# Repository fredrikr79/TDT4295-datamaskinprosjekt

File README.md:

## Structure

### MCU

The source code for the microcontroller

### FPGA

The source code for the FPGA

### PCB

The schematics for the PCB

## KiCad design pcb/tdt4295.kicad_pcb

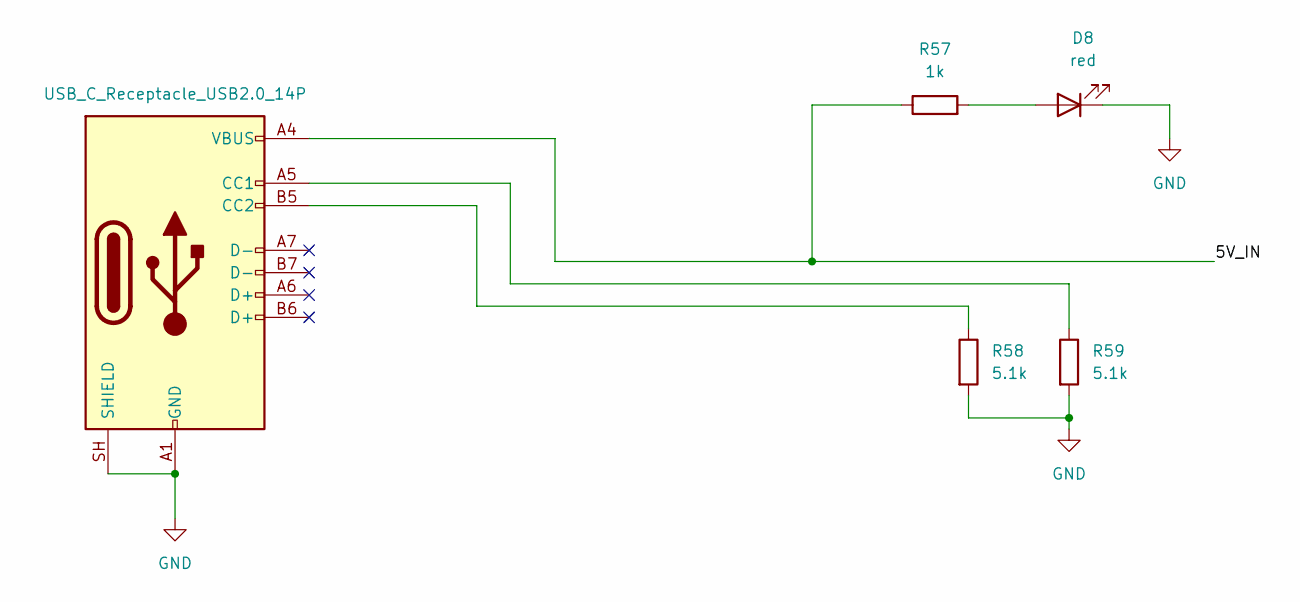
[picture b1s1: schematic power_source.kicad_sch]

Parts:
D8: red; LED_0805_2012Metric_Pad1.15x1.40mm_HandSolder
J7: USB_C_Receptacle_USB2.0_14P; USB_C_Receptacle_GCT_USB4105-xx-A_16P_TopMnt_Horizontal
R57: 1k; R_0805_2012Metric_Pad1.20x1.40mm_HandSolder
R58, R59: 5.1k; R_0805_2012Metric_Pad1.20x1.40mm_HandSolder

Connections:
5V_IN: J7.A4 (VBUS), J7.A9 (VBUS), J7.B4 (VBUS), J7.B9 (VBUS), R57.1; also elsewhere on the board
GND: D8.1 (K), J7.A1 (GND), J7.A12 (GND), J7.B1 (GND), J7.B12 (GND), J7.SH (SHIELD), R58.2, R59.2; also elsewhere on the board
unnamed: D8.2 (A), R57.2
unnamed: J7.A5 (CC1), R59.1
unnamed: J7.B5 (CC2), R58.1

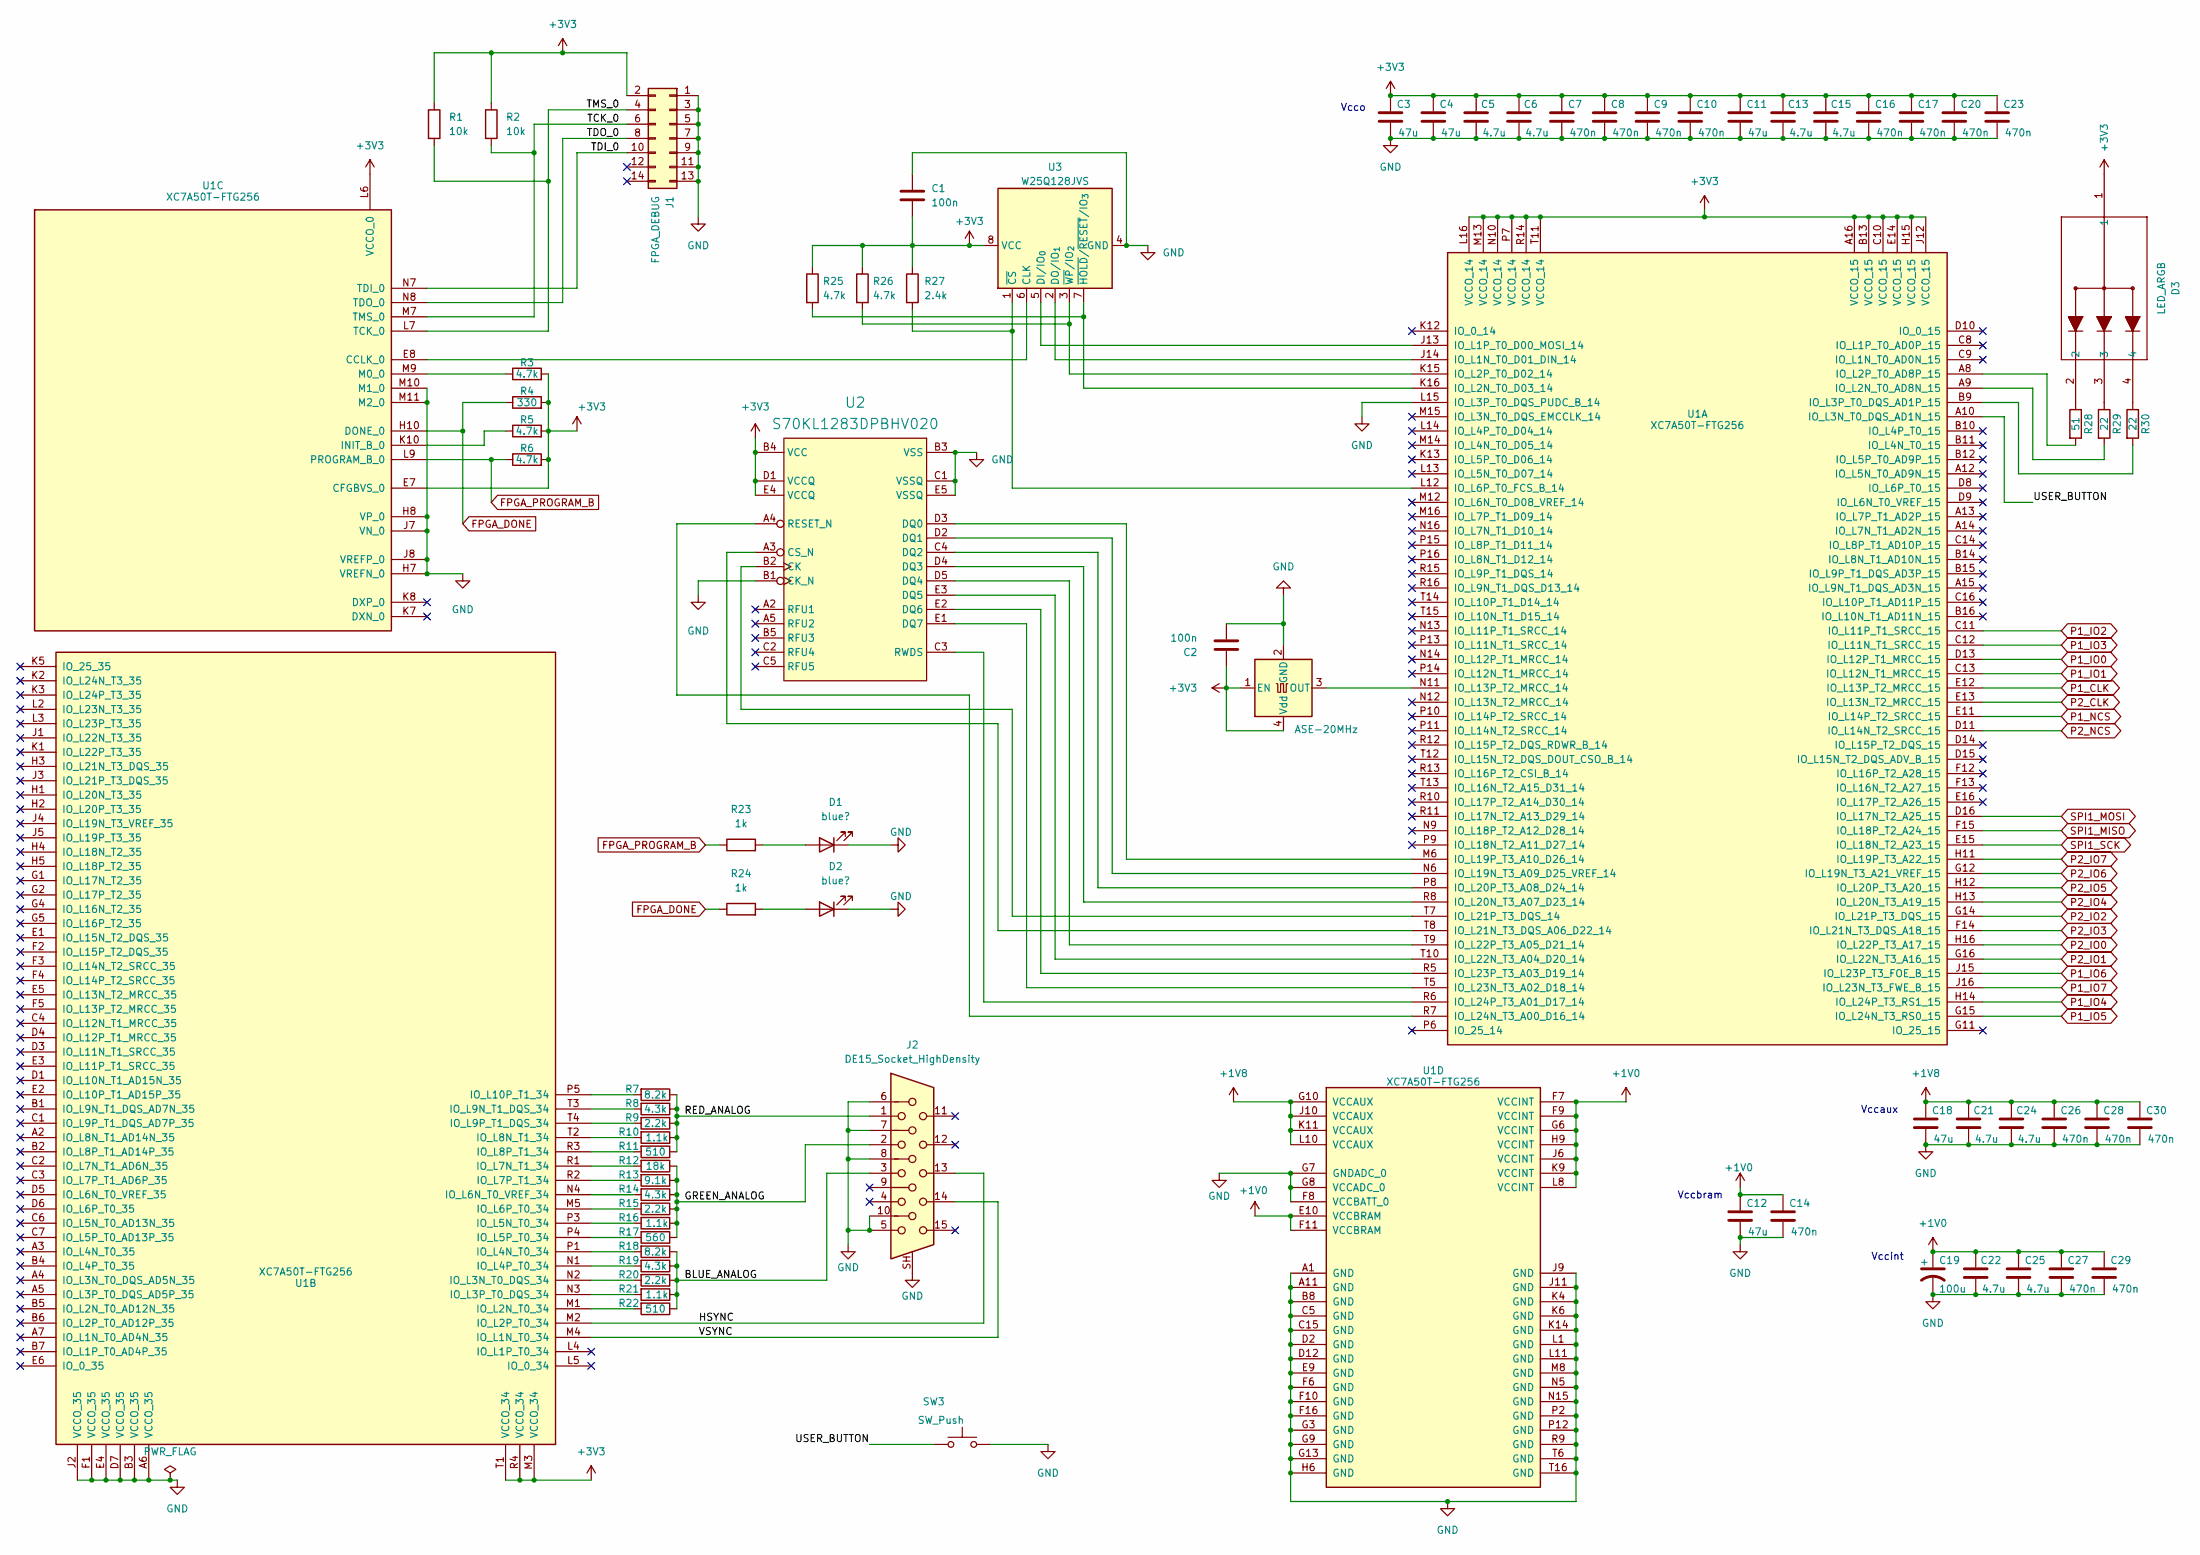
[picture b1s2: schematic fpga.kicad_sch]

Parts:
C1, C2: 100n; C_0805_2012Metric_Pad1.18x1.45mm_HandSolder
C3, C4, C11, C12, C18: 47u; C_0805_2012Metric_Pad1.18x1.45mm_HandSolder
C5, C6, C13, C15, C21, C22, C24, C25: 4.7u; C_0805_2012Metric_Pad1.18x1.45mm_HandSolder
C7, C8, C9, C10, C14, C16, C17, C20, C23, C26, C27, C28, C29, C30: 470n; C_0805_2012Metric_Pad1.18x1.45mm_HandSolder
C19: 100u; C_0805_2012Metric_Pad1.18x1.45mm_HandSolder
D1, D2: blue?; LED_0805_2012Metric_Pad1.15x1.40mm_HandSolder
D3: LED_ARGB; SON4_APTF1616LSEEZGKQBKC_KNB
J1: FPGA_DEBUG; PinHeader_2x07_P2.54mm_Vertical
J2: DE15_Socket_HighDensity; AMPHENOL_L77HDE15SD1CH4FVGA
R1, R2: 10k; R_0805_2012Metric_Pad1.20x1.40mm_HandSolder
R3, R5, R6, R25, R26: 4.7k; R_0805_2012Metric_Pad1.20x1.40mm_HandSolder
R4: 330; R_0805_2012Metric_Pad1.20x1.40mm_HandSolder
R7, R18: 8.2k; R_0805_2012Metric_Pad1.20x1.40mm_HandSolder
R8, R14, R19: 4.3k; R_0805_2012Metric_Pad1.20x1.40mm_HandSolder
R9, R15, R20: 2.2k; R_0805_2012Metric_Pad1.20x1.40mm_HandSolder
R10, R16, R21: 1.1k; R_0805_2012Metric_Pad1.20x1.40mm_HandSolder
R11, R22: 510; R_0805_2012Metric_Pad1.20x1.40mm_HandSolder
R12: 18k; R_0805_2012Metric_Pad1.20x1.40mm_HandSolder
R13: 9.1k; R_0805_2012Metric_Pad1.20x1.40mm_HandSolder
R17: 560; R_0805_2012Metric_Pad1.20x1.40mm_HandSolder
R23, R24: 1k; R_0805_2012Metric_Pad1.20x1.40mm_HandSolder
R27: 2.4k; R_0805_2012Metric_Pad1.20x1.40mm_HandSolder
R28: 51; R_0805_2012Metric_Pad1.20x1.40mm_HandSolder
R29, R30: 22; R_0805_2012Metric_Pad1.20x1.40mm_HandSolder
SW3: SW_Push; SW_Push_1P1T_NO_CK_KSC6xxG
U1: XC7A50T-FTG256; Xilinx_FTG256
U2: S70KL1283DPBHV020; BGA24C100P5X5_600X800X100
U3: W25Q128JVS; SOIC-8_5.3x5.3mm_P1.27mm
Y1: ASE-20MHz; Oscillator_SMD_Abracon_ASV-4Pin_7.0x5.1mm_HandSoldering

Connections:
+1V0: C12.1, C14.1, C19.1, C22.1, C25.1, C27.1, C29.1, U1.E10 (VCCBRAM), U1.F7 (VCCINT), U1.F9 (VCCINT), U1.F11 (VCCBRAM), U1.G6 (VCCINT), U1.H9 (VCCINT), U1.J6 (VCCINT), U1.K9 (VCCINT), U1.L8 (VCCINT); also elsewhere on the board
+1V8: C18.1, C21.1, C24.1, C26.1, C28.1, C30.1, U1.G10 (VCCAUX), U1.J10 (VCCAUX), U1.K11 (VCCAUX), U1.L10 (VCCAUX); also elsewhere on the board
+3V3: C1.2, C2.1, C3.1, C4.1, C5.1, C6.1, C7.1, C8.1, C9.1, C10.1, C11.1, C13.1, C15.1, C16.1, C17.1, C20.1, C23.1, D3.1, J1.2, R1.1, R2.1, R3.2, R4.2, R5.2, R6.2, R25.1, R26.1, R27.1, U1.A16 (VCCO_15), U1.B13 (VCCO_15), U1.C10 (VCCO_15), U1.E7 (CFGBVS_0), U1.E14 (VCCO_15), U1.H15 (VCCO_15), U1.J12 (VCCO_15), U1.L6 (VCCO_0), U1.L16 (VCCO_14), U1.M3 (VCCO_34), U1.M13 (VCCO_14), U1.N10 (VCCO_14), U1.P7 (VCCO_14), U1.R4 (VCCO_34), U1.R14 (VCCO_14), U1.T1 (VCCO_34), U1.T11 (VCCO_14), U2.B4 (VCC), U2.D1 (VCCQ), U2.E4 (VCCQ), U3.8 (VCC), Y1.1 (EN), Y1.4 (Vdd); also elsewhere on the board
/fpga/BLUE_ANALOG: J2.3, R18.1, R19.1, R20.1, R21.1, R22.1
/fpga/GREEN_ANALOG: J2.2, R12.1, R13.1, R14.1, R15.1, R16.1, R17.1
/fpga/HSYNC: J2.13, U1.M2 (IO_L2P_T0_34)
/fpga/RED_ANALOG: J2.1, R7.1, R8.1, R9.1, R10.1, R11.1
/fpga/TCK_0: J1.6, R2.2, U1.M7 (TMS_0)
/fpga/TDI_0: J1.10, U1.N7 (TDI_0)
/fpga/TDO_0: J1.8, U1.N8 (TDO_0)
/fpga/TMS_0: J1.4, R1.2, U1.L7 (TCK_0)
/fpga/USER_BUTTON: SW3.1, U1.A10 (IO_L3N_T0_DQS_AD1N_15)
/fpga/VSYNC: J2.14, U1.M4 (IO_L1N_T0_34)
FPGA_DONE: R4.1, R24.1, U1.H10 (DONE_0); also elsewhere on the board
FPGA_PROGRAM_B: R6.1, R23.1, U1.L9 (PROGRAM_B_0); also elsewhere on the board
GND: C1.1, C2.2, C3.2, C4.2, C5.2, C6.2, C7.2, C8.2, C9.2, C10.2, C11.2, C12.2, C13.2, C14.2, C15.2, C16.2, C17.2, C18.2, C19.2, C20.2, C21.2, C22.2, C23.2, C24.2, C25.2, C26.2, C27.2, C28.2, C29.2, C30.2, D1.1 (K), D2.1 (K), J1.1, J1.3, J1.5, J1.7, J1.9, J1.11, J1.13, J2.5, J2.6, J2.7, J2.8, J2.10, J2.SH, SW3.2, U1.A1 (GND), U1.A6 (VCCO_35), U1.A11 (GND), U1.B3 (VCCO_35), U1.B8 (GND), U1.C5 (GND), U1.C15 (GND), U1.D2 (GND), U1.D7 (VCCO_35), U1.D12 (GND), U1.E4 (VCCO_35), U1.E9 (GND), U1.F1 (VCCO_35), U1.F6 (GND), U1.F8 (VCCBATT_0), U1.F10 (GND), U1.F16 (GND), U1.G3 (GND), U1.G7 (GNDADC_0), U1.G8 (VCCADC_0), U1.G9 (GND), U1.G13 (GND), U1.H6 (GND), U1.H7 (VREFN_0), U1.H8 (VP_0), U1.J2 (VCCO_35), U1.J7 (VN_0), U1.J8 (VREFP_0), U1.J9 (GND), U1.J11 (GND), U1.K4 (GND), U1.K6 (GND), U1.K14 (GND), U1.L1 (GND), U1.L11 (GND), U1.L15 (IO_L3P_T0_DQS_PUDC_B_14), U1.M8 (GND), U1.M10 (M1_0), U1.M11 (M2_0), U1.N5 (GND), U1.N15 (GND), U1.P2 (GND), U1.P12 (GND), U1.R9 (GND), U1.T6 (GND), U1.T16 (GND), U2.B1 (CK_N), U2.B3 (VSS), U2.C1 (VSSQ), U2.E5 (VSSQ), U3.4 (GND), Y1.2 (GND); also elsewhere on the board
unnamed: D1.2 (A), R23.2
unnamed: D2.2 (A), R24.2
unnamed: D3.2, R28.1
unnamed: D3.3, R29.1
unnamed: D3.4, R30.1
unnamed: U1.J14 (IO_L1N_T0_D01_DIN_14), U3.2 (DO/IO_{1})
unnamed: U1.J13 (IO_L1P_T0_D00_MOSI_14), U3.5 (DI/IO_{0})
unnamed: R29.2, U1.A9 (IO_L2N_T0_AD8N_15)
unnamed: R25.2, U1.K16 (IO_L2N_T0_D03_14), U3.7 (~HOLD/~RESET/IO_{3})
unnamed: R28.2, U1.A8 (IO_L2P_T0_AD8P_15)
unnamed: R26.2, U1.K15 (IO_L2P_T0_D02_14), U3.3 (~WP/IO_{2})
unnamed: R30.2, U1.B9 (IO_L3P_T0_DQS_AD1P_15)
unnamed: R27.2, U1.L12 (IO_L6P_T0_FCS_B_14), U3.1 (~CS)
unnamed: U1.N11 (IO_L13P_T2_MRCC_14), Y1.3 (OUT)
unnamed: U1.N6 (IO_L19N_T3_A09_D25_VREF_14), U2.D2 (DQ1)
unnamed: U1.M6 (IO_L19P_T3_A10_D26_14), U2.D3 (DQ0)
unnamed: U1.R8 (IO_L20N_T3_A07_D23_14), U2.D4 (DQ3)
unnamed: U1.P8 (IO_L20P_T3_A08_D24_14), U2.C4 (DQ2)
unnamed: U1.T8 (IO_L21N_T3_DQS_A06_D22_14), U2.A3 (CS_N)
unnamed: U1.T7 (IO_L21P_T3_DQS_14), U2.B2 (CK)
unnamed: U1.T10 (IO_L22N_T3_A04_D20_14), U2.E3 (DQ5)
unnamed: U1.T9 (IO_L22P_T3_A05_D21_14), U2.D5 (DQ4)
unnamed: U1.T5 (IO_L23N_T3_A02_D18_14), U2.E1 (DQ7)
unnamed: U1.R5 (IO_L23P_T3_A03_D19_14), U2.E2 (DQ6)
unnamed: U1.R7 (IO_L24N_T3_A00_D16_14), U2.A4 (RESET_N)
unnamed: U1.R6 (IO_L24P_T3_A01_D17_14), U2.C3 (RWDS)
unnamed: R22.2, U1.M1 (IO_L2N_T0_34)
unnamed: R20.2, U1.N2 (IO_L3N_T0_DQS_34)
unnamed: R21.2, U1.N3 (IO_L3P_T0_DQS_34)
unnamed: R18.2, U1.P1 (IO_L4N_T0_34)
unnamed: R19.2, U1.N1 (IO_L4P_T0_34)
unnamed: R16.2, U1.P3 (IO_L5N_T0_34)
unnamed: R17.2, U1.P4 (IO_L5P_T0_34)
unnamed: R14.2, U1.N4 (IO_L6N_T0_VREF_34)
unnamed: R15.2, U1.M5 (IO_L6P_T0_34)
unnamed: R12.2, U1.R1 (IO_L7N_T1_34)
unnamed: R13.2, U1.R2 (IO_L7P_T1_34)
unnamed: R10.2, U1.T2 (IO_L8N_T1_34)
unnamed: R11.2, U1.R3 (IO_L8P_T1_34)
unnamed: R8.2, U1.T3 (IO_L9N_T1_DQS_34)
unnamed: R9.2, U1.T4 (IO_L9P_T1_DQS_34)
unnamed: R7.2, U1.P5 (IO_L10P_T1_34)
unnamed: U1.E8 (CCLK_0), U3.6 (CLK)
unnamed: R5.1, U1.K10 (INIT_B_0)
unnamed: R3.1, U1.M9 (M0_0)
P1_CLK: U1.E12 (IO_L13P_T2_MRCC_15); also elsewhere on the board
P1_IO0: U1.D13 (IO_L12P_T1_MRCC_15); also elsewhere on the board
P1_IO1: U1.C13 (IO_L12N_T1_MRCC_15); also elsewhere on the board
P1_IO2: U1.C11 (IO_L11P_T1_SRCC_15); also elsewhere on the board
P1_IO3: U1.C12 (IO_L11N_T1_SRCC_15); also elsewhere on the board
P1_IO4: U1.H14 (IO_L24P_T3_RS1_15); also elsewhere on the board
P1_IO5: U1.G15 (IO_L24N_T3_RS0_15); also elsewhere on the board
P1_IO6: U1.J15 (IO_L23P_T3_FOE_B_15); also elsewhere on the board
P1_IO7: U1.J16 (IO_L23N_T3_FWE_B_15); also elsewhere on the board
P1_NCS: U1.E11 (IO_L14P_T2_SRCC_15); also elsewhere on the board
P2_CLK: U1.E13 (IO_L13N_T2_MRCC_15); also elsewhere on the board
P2_IO0: U1.H16 (IO_L22P_T3_A17_15); also elsewhere on the board
P2_IO1: U1.G16 (IO_L22N_T3_A16_15); also elsewhere on the board
P2_IO2: U1.G14 (IO_L21P_T3_DQS_15); also elsewhere on the board
P2_IO3: U1.F14 (IO_L21N_T3_DQS_A18_15); also elsewhere on the board
P2_IO4: U1.H13 (IO_L20N_T3_A19_15); also elsewhere on the board
P2_IO5: U1.H12 (IO_L20P_T3_A20_15); also elsewhere on the board
P2_IO6: U1.G12 (IO_L19N_T3_A21_VREF_15); also elsewhere on the board
P2_IO7: U1.H11 (IO_L19P_T3_A22_15); also elsewhere on the board
P2_NCS: U1.D11 (IO_L14N_T2_SRCC_15); also elsewhere on the board
SPI1_MISO: U1.F15 (IO_L18P_T2_A24_15); also elsewhere on the board
SPI1_MOSI: U1.D16 (IO_L17N_T2_A25_15); also elsewhere on the board
SPI1_SCK: U1.E15 (IO_L18N_T2_A23_15); also elsewhere on the board

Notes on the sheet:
Vccbram
Vccaux
Vccint
Vcco

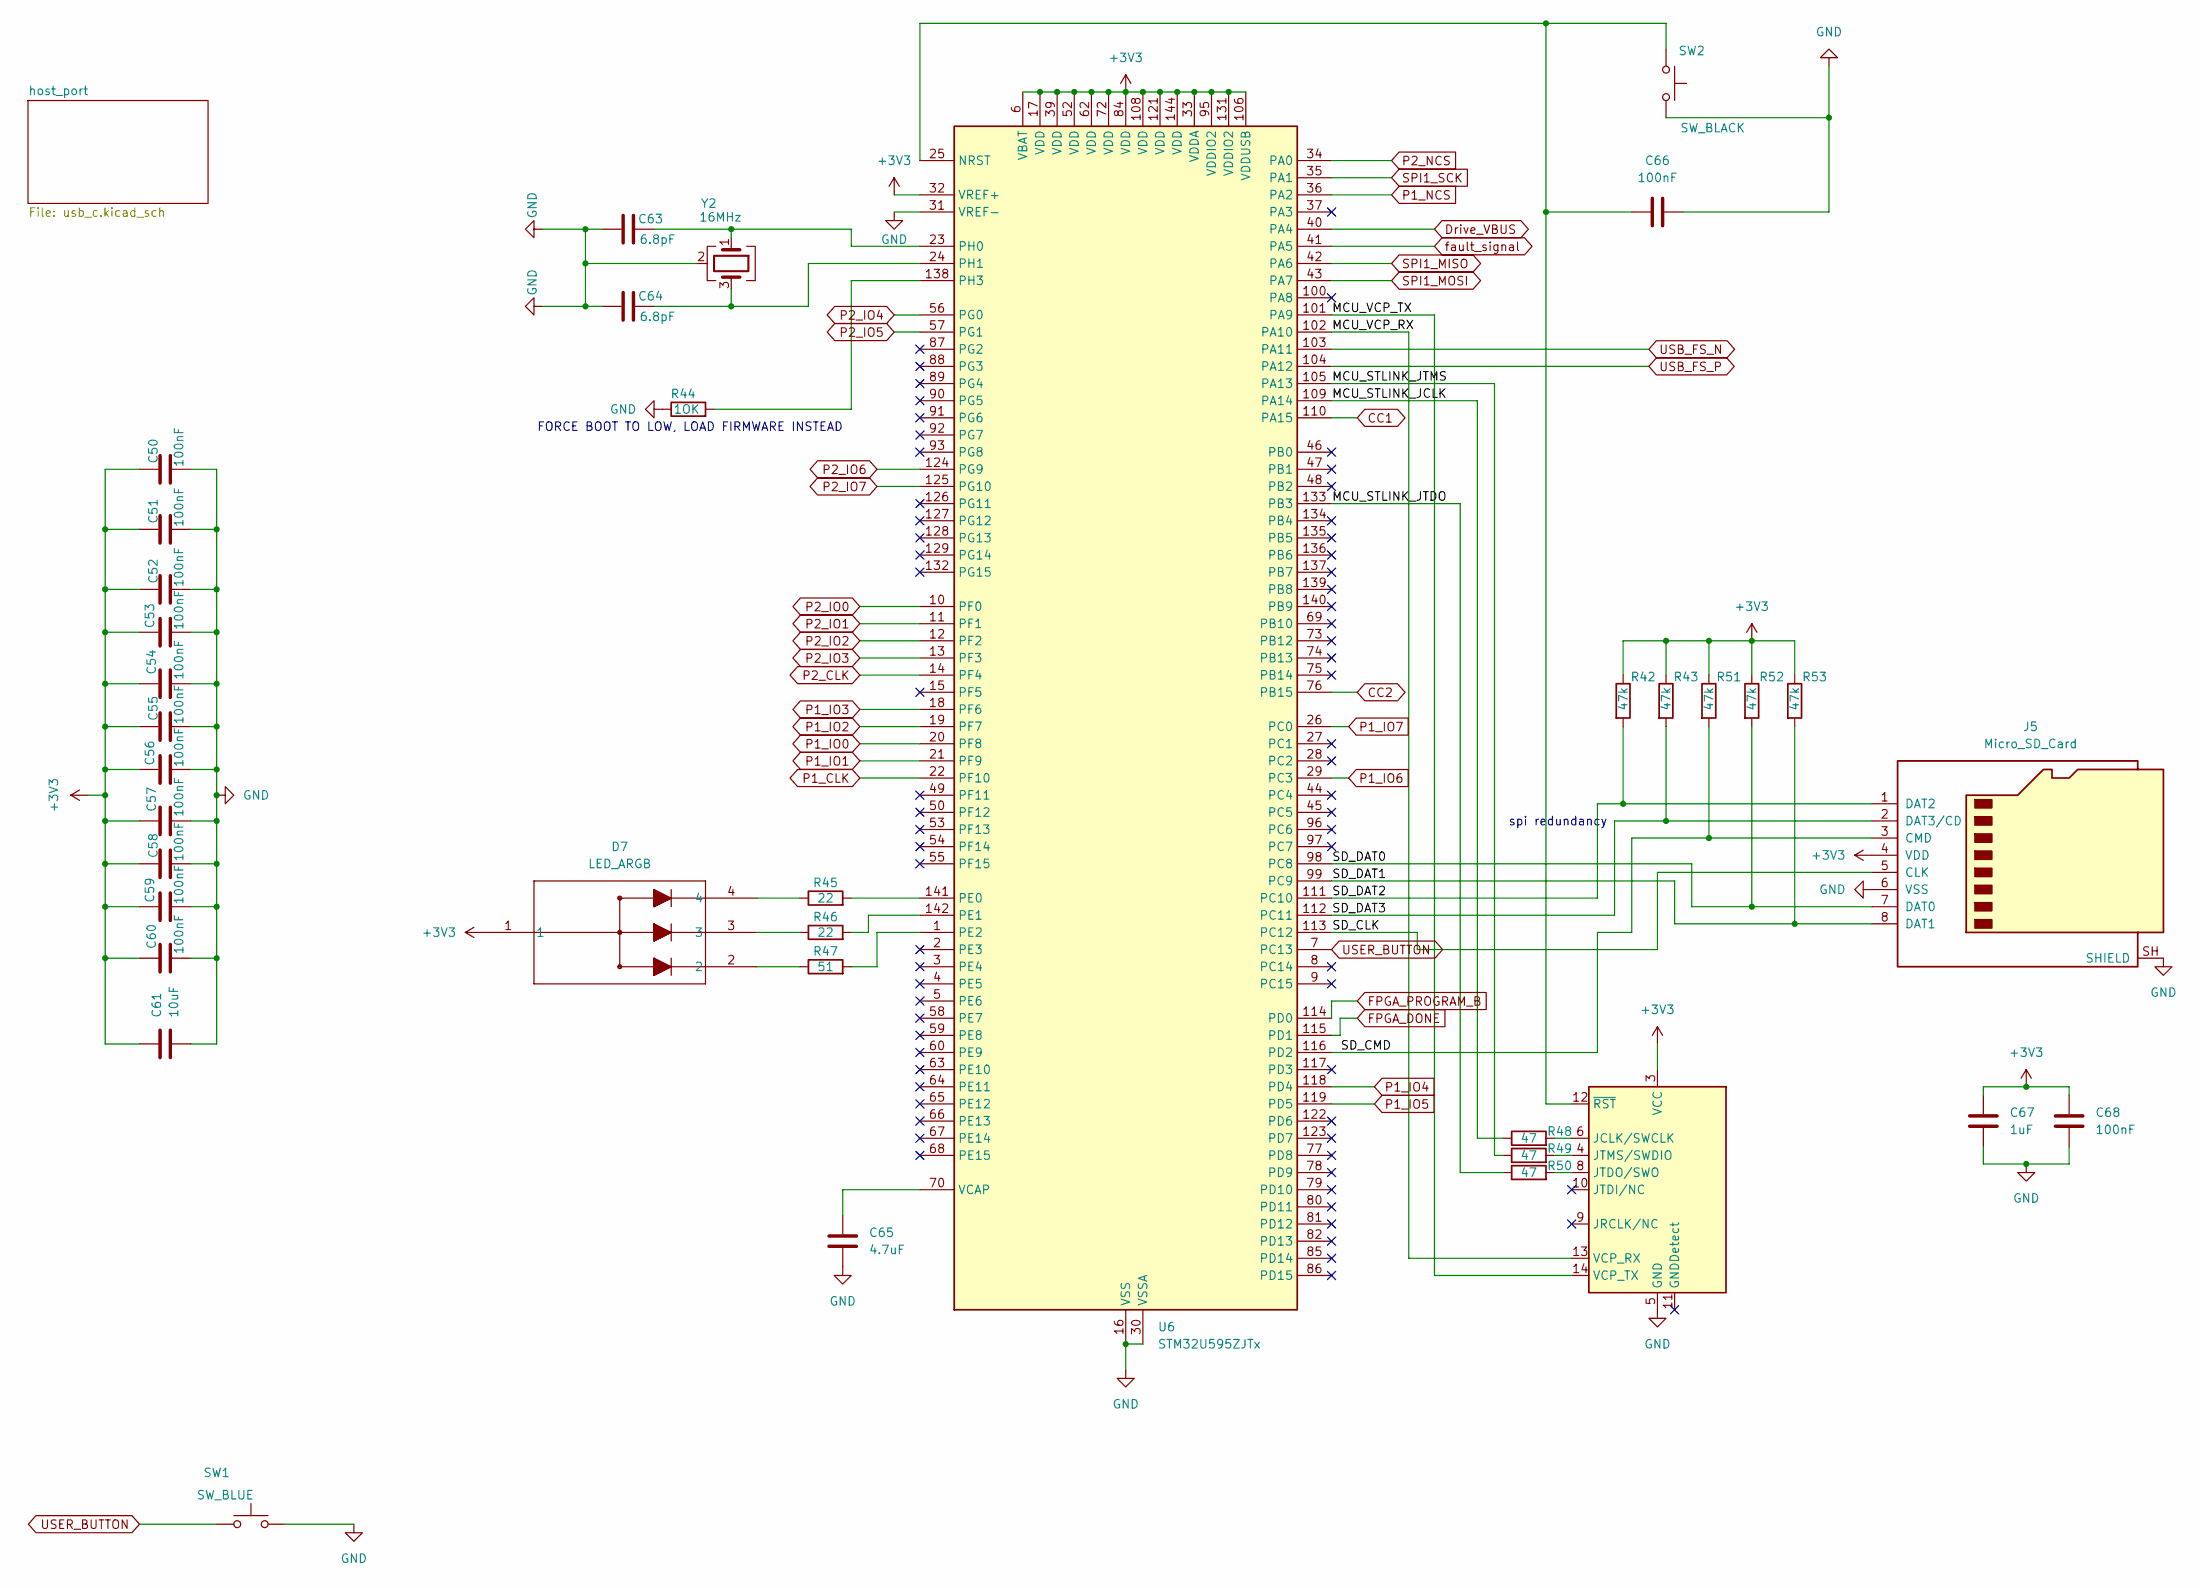
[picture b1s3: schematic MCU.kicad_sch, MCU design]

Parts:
C50, C51, C52, C53, C54, C55, C56, C57, C58, C59, C60, C66, C68: 100nF; C_0805_2012Metric_Pad1.18x1.45mm_HandSolder
C61: 10uF; C_0805_2012Metric_Pad1.18x1.45mm_HandSolder
C63, C64: 6.8pF; C_0805_2012Metric_Pad1.18x1.45mm_HandSolder
C65: 4.7uF; C_0805_2012Metric_Pad1.18x1.45mm_HandSolder
C67: 1uF; C_0805_2012Metric_Pad1.18x1.45mm_HandSolder
D7: LED_ARGB; SON4_APTF1616LSEEZGKQBKC_KNB
J4: Conn_ST_STDC14; PinHeader_2x07_P1.27mm_Vertical_SMD
J5: Micro_SD_Card; microSD_HC_Molex_47219-2001
R42, R43, R51, R52, R53: 47k; R_0805_2012Metric_Pad1.20x1.40mm_HandSolder
R44: 1OK; R_0805_2012Metric_Pad1.20x1.40mm_HandSolder
R45, R46: 22; R_0805_2012Metric_Pad1.20x1.40mm_HandSolder
R47: 51; R_0805_2012Metric_Pad1.20x1.40mm_HandSolder
R48, R49, R50: 47; R_0805_2012Metric_Pad1.20x1.40mm_HandSolder
SW1: SW_BLUE; SW_Push_1P1T_NO_CK_KSC6xxG
SW2: SW_BLACK; SW_Push_1P1T_NO_CK_KSC6xxG
U6: STM32U595ZJTx; LQFP-144_20x20mm_P0.5mm
Y2: 16MHz; Crystal_SMD_3225-4Pin_3.2x2.5mm

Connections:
+3V3: C50.1, C51.1, C52.1, C53.1, C54.1, C55.1, C56.1, C57.1, C58.1, C59.1, C60.1, C61.1, C67.1, C68.1, D7.1, J4.3 (VCC), J5.4 (VDD), R42.1, R43.1, R51.1, R52.1, R53.1, U6.6 (VBAT), U6.17 (VDD), U6.32 (VREF+), U6.33 (VDDA), U6.39 (VDD), U6.52 (VDD), U6.62 (VDD), U6.72 (VDD), U6.84 (VDD), U6.95 (VDDIO2), U6.106 (VDDUSB), U6.108 (VDD), U6.121 (VDD), U6.131 (VDDIO2), U6.144 (VDD); also elsewhere on the board
/MCU/MCU_STLINK_JCLK: R48.1, U6.109 (PA14)
/MCU/MCU_STLINK_JTDO: R50.1, U6.133 (PB3)
/MCU/MCU_STLINK_JTMS: R49.1, U6.105 (PA13)
/MCU/MCU_VCP_RX: J4.13 (VCP_RX), U6.102 (PA10)
/MCU/MCU_VCP_TX: J4.14 (VCP_TX), U6.101 (PA9)
/MCU/SD_CLK: J5.5 (CLK), U6.113 (PC12)
/MCU/SD_CMD: J5.3 (CMD), R51.2, U6.116 (PD2)
/MCU/SD_DAT0: J5.7 (DAT0), R52.2, U6.98 (PC8)
/MCU/SD_DAT1: J5.8 (DAT1), R53.2, U6.99 (PC9)
/MCU/SD_DAT2: J5.1 (DAT2), R42.2, U6.111 (PC10)
/MCU/SD_DAT3: J5.2 (DAT3/CD), R43.2, U6.112 (PC11)
/MCU/USER_BUTTON: SW1.1, U6.7 (PC13)
CC1: U6.110 (PA15); also elsewhere on the board
CC2: U6.76 (PB15); also elsewhere on the board
Drive_VBUS: U6.40 (PA4); also elsewhere on the board
FPGA_DONE: U6.115 (PD1); also elsewhere on the board
FPGA_PROGRAM_B: U6.114 (PD0); also elsewhere on the board
GND: C50.2, C51.2, C52.2, C53.2, C54.2, C55.2, C56.2, C57.2, C58.2, C59.2, C60.2, C61.2, C63.1, C64.1, C65.2, C66.1, C67.2, C68.2, J4.5 (GND), J4.7 (GND), J5.6 (VSS), J5.SH (SHIELD), R44.1, SW1.2, SW2.2, U6.16 (VSS), U6.30 (VSSA), U6.31 (VREF-), U6.38 (VSS), U6.51 (VSS), U6.61 (VSS), U6.71 (VSS), U6.83 (VSS), U6.94 (VSS), U6.107 (VSS), U6.120 (VSS), U6.130 (VSS), U6.143 (VSS), Y2.2 (G), Y2.4 (G); also elsewhere on the board
unnamed: D7.2, R47.1
unnamed: D7.3, R46.1
unnamed: D7.4, R45.1
unnamed: J4.6 (JCLK/SWCLK), R48.2
unnamed: J4.8 (JTDO/SWO), R50.2
unnamed: J4.4 (JTMS/SWDIO), R49.2
unnamed: C66.2, J4.12 (~RST), SW2.1, U6.25 (NRST)
unnamed: R45.2, U6.141 (PE0)
unnamed: R46.2, U6.142 (PE1)
unnamed: R47.2, U6.1 (PE2)
unnamed: C63.2, U6.23 (PH0), Y2.1
unnamed: C64.2, U6.24 (PH1), Y2.3
unnamed: R44.2, U6.138 (PH3)
unnamed: C65.1, U6.70 (VCAP)
P1_CLK: U6.22 (PF10); also elsewhere on the board
P1_IO0: U6.20 (PF8); also elsewhere on the board
P1_IO1: U6.21 (PF9); also elsewhere on the board
P1_IO2: U6.19 (PF7); also elsewhere on the board
P1_IO3: U6.18 (PF6); also elsewhere on the board
P1_IO4: U6.118 (PD4); also elsewhere on the board
P1_IO5: U6.119 (PD5); also elsewhere on the board
P1_IO6: U6.29 (PC3); also elsewhere on the board
P1_IO7: U6.26 (PC0); also elsewhere on the board
P1_NCS: U6.36 (PA2); also elsewhere on the board
P2_CLK: U6.14 (PF4); also elsewhere on the board
P2_IO0: U6.10 (PF0); also elsewhere on the board
P2_IO1: U6.11 (PF1); also elsewhere on the board
P2_IO2: U6.12 (PF2); also elsewhere on the board
P2_IO3: U6.13 (PF3); also elsewhere on the board
P2_IO4: U6.56 (PG0); also elsewhere on the board
P2_IO5: U6.57 (PG1); also elsewhere on the board
P2_IO6: U6.124 (PG9); also elsewhere on the board
P2_IO7: U6.125 (PG10); also elsewhere on the board
P2_NCS: U6.34 (PA0); also elsewhere on the board
SPI1_MISO: U6.42 (PA6); also elsewhere on the board
SPI1_MOSI: U6.43 (PA7); also elsewhere on the board
SPI1_SCK: U6.35 (PA1); also elsewhere on the board
fault_signal: U6.41 (PA5); also elsewhere on the board

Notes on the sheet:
FORCE BOOT TO LOW, LOAD FIRMWARE INSTEAD
spi redundancy

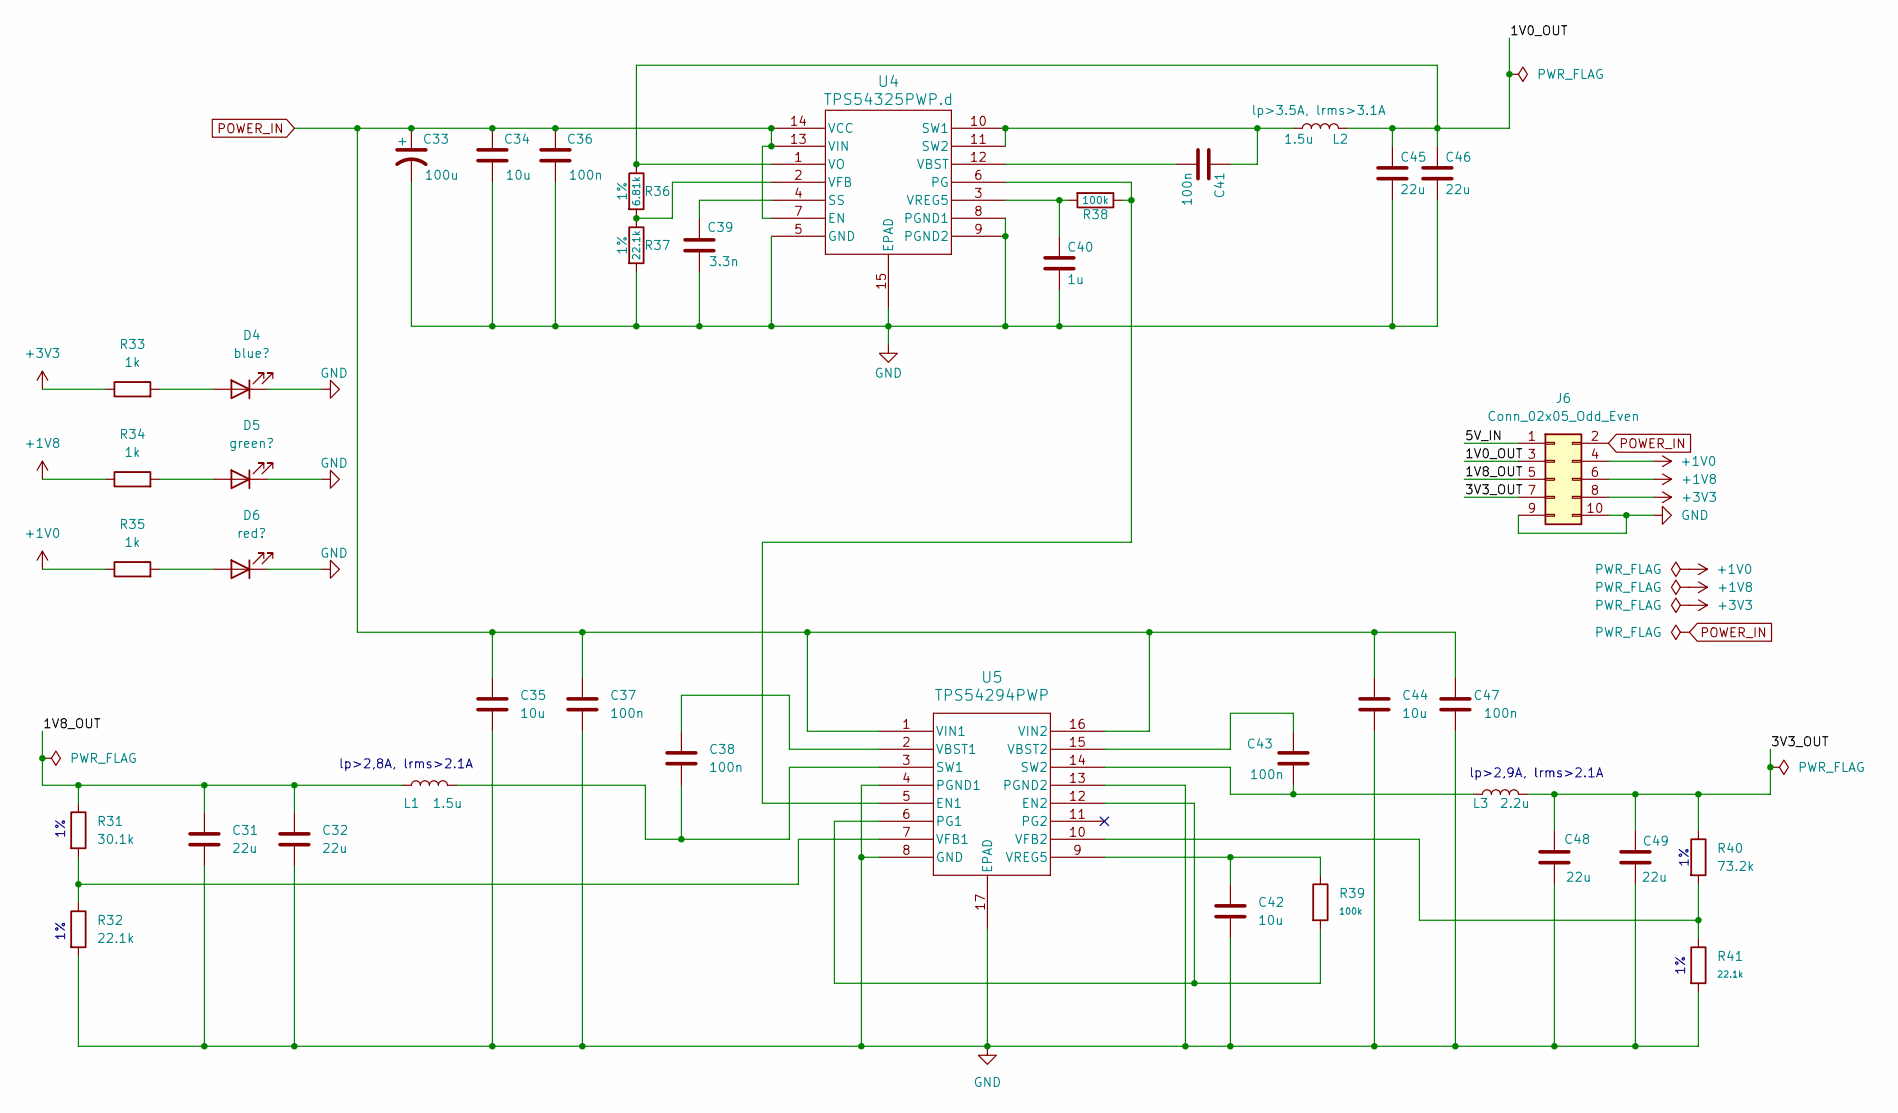
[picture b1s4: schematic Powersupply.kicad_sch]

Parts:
C31, C32, C45, C46, C48, C49: 22u; C_0805_2012Metric_Pad1.18x1.45mm_HandSolder
C33: 100u; C_0805_2012Metric_Pad1.18x1.45mm_HandSolder
C34, C35, C42, C44: 10u; C_0805_2012Metric_Pad1.18x1.45mm_HandSolder
C36, C37, C38, C41, C43, C47: 100n; C_0805_2012Metric_Pad1.18x1.45mm_HandSolder
C39: 3.3n; C_0805_2012Metric_Pad1.18x1.45mm_HandSolder
C40: 1u; C_0805_2012Metric_Pad1.18x1.45mm_HandSolder
D4: blue?; LED_0805_2012Metric_Pad1.15x1.40mm_HandSolder
D5: green?; LED_0805_2012Metric_Pad1.15x1.40mm_HandSolder
D6: red?; LED_0805_2012Metric_Pad1.15x1.40mm_HandSolder
J6: Conn_02x05_Odd_Even; PinHeader_2x05_P2.54mm_Vertical_SMD
L1, L2: 1.5u; L_0805_2012Metric_Pad1.05x1.20mm_HandSolder
L3: 2.2u; L_0805_2012Metric_Pad1.05x1.20mm_HandSolder
R31: 30.1k; R_0805_2012Metric_Pad1.20x1.40mm_HandSolder
R32, R37, R41: 22.1k; R_0805_2012Metric_Pad1.20x1.40mm_HandSolder
R33, R34, R35: 1k; R_0805_2012Metric_Pad1.20x1.40mm_HandSolder
R36: 6.81k; R_0805_2012Metric_Pad1.20x1.40mm_HandSolder
R38, R39: 100k; R_0805_2012Metric_Pad1.20x1.40mm_HandSolder
R40: 73.2k; R_0805_2012Metric_Pad1.20x1.40mm_HandSolder
U4: TPS54325PWP.d; PWP14_2P31X2P46
U5: TPS54294PWP; HTSSOP-16-1EP_4.4x5mm_P0.65mm_EP3.4x5mm_Mask2.46x2.31mm

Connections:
5V_IN: J6.1; also elsewhere on the board
+1V0: J6.4, R35.1; also elsewhere on the board
+1V8: J6.6, R34.1; also elsewhere on the board
+3V3: J6.8, R33.1; also elsewhere on the board
/Powersupply/1V0_OUT: C45.1, C46.1, J6.3, L2.1, R36.1, U4.1 (VO)
/Powersupply/1V8_OUT: C31.1, C32.1, J6.5, L1.1, R31.1
/Powersupply/3V3_OUT: C48.1, C49.1, J6.7, L3.2, R40.1
GND: C31.2, C32.2, C33.2, C34.2, C35.2, C36.2, C37.2, C39.2, C40.2, C42.2, C44.2, C45.2, C46.2, C47.2, C48.2, C49.2, D4.1 (K), D5.1 (K), D6.1 (K), J6.9, J6.10, R32.2, R37.2, R41.2, U4.5 (GND), U4.8 (PGND1), U4.9 (PGND2), U4.15 (EPAD), U5.4 (PGND1), U5.8 (GND), U5.13 (PGND2), U5.17 (EPAD), U5.EPAD; also elsewhere on the board
unnamed: D4.2 (A), R33.2
unnamed: D5.2 (A), R34.2
unnamed: D6.2 (A), R35.2
unnamed: R38.1, U4.6 (PG), U5.5 (EN1)
unnamed: C39.1, U4.4 (SS)
unnamed: C41.1, L2.2, U4.10 (SW1), U4.11 (SW2)
unnamed: C41.2, U4.12 (VBST)
unnamed: R36.2, R37.1, U4.2 (VFB)
unnamed: C40.1, R38.2, U4.3 (VREG5)
unnamed: R39.2, U5.6 (PG1), U5.12 (EN2)
unnamed: C38.2, L1.2, U5.3 (SW1)
unnamed: C43.2, L3.1, U5.14 (SW2)
unnamed: C38.1, U5.2 (VBST1)
unnamed: C43.1, U5.15 (VBST2)
unnamed: R31.2, R32.1, U5.7 (VFB1)
unnamed: R40.2, R41.1, U5.10 (VFB2)
unnamed: C42.1, R39.1, U5.9 (VREG5)
POWER_IN: C33.1, C34.1, C35.1, C36.1, C37.1, C44.1, C47.1, J6.2, U4.7 (EN), U4.13 (VIN), U4.14 (VCC), U5.1 (VIN1), U5.16 (VIN2); also elsewhere on the board

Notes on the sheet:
lp>2,9A, lrms>2.1A
lp>2,8A, lrms>2.1A

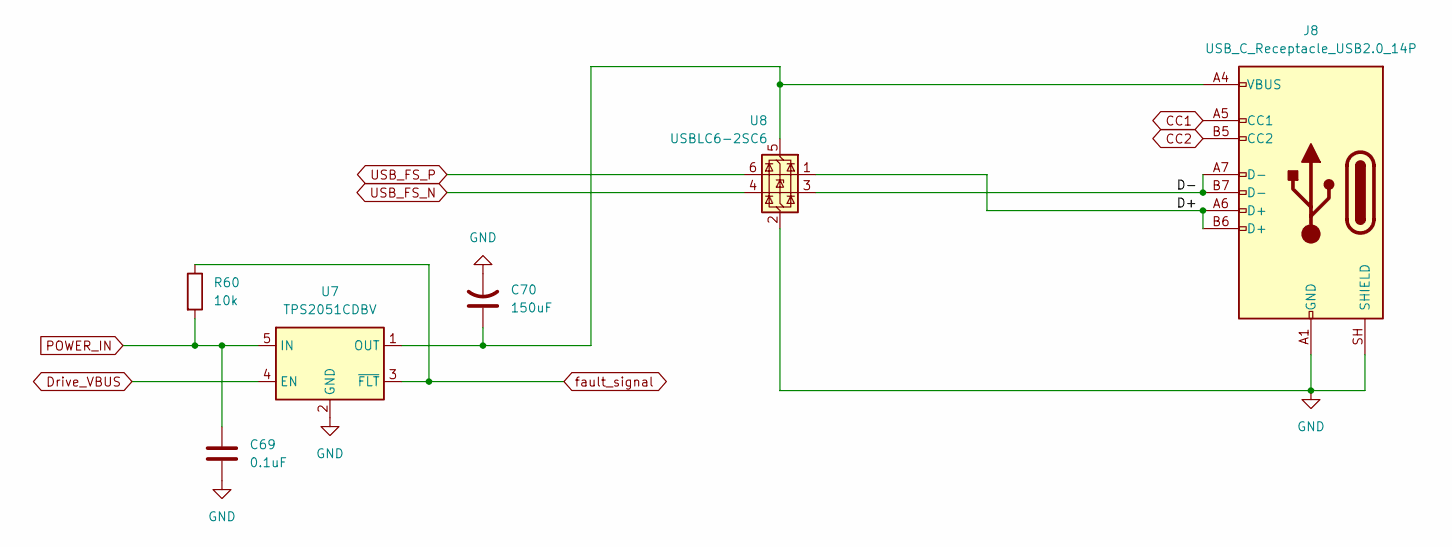
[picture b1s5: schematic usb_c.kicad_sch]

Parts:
C69: 0.1uF; C_0805_2012Metric_Pad1.18x1.45mm_HandSolder
C70: 150uF; C_0805_2012Metric_Pad1.18x1.45mm_HandSolder
J8: USB_C_Receptacle_USB2.0_14P; USB_C_Receptacle_GCT_USB4105-xx-A_16P_TopMnt_Horizontal
R60: 10k; R_0805_2012Metric_Pad1.20x1.40mm_HandSolder
U7: TPS2051CDBV; SOT-23-5
U8: USBLC6-2SC6; SOT-23-6

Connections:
CC1: J8.A5 (CC1); also elsewhere on the board
CC2: J8.B5 (CC2); also elsewhere on the board
Drive_VBUS: U7.4 (EN); also elsewhere on the board
GND: C69.2, C70.2, J8.A1 (GND), J8.A12 (GND), J8.B1 (GND), J8.B12 (GND), J8.SH (SHIELD), U7.2 (GND), U8.2 (GND); also elsewhere on the board
unnamed: C70.1, J8.A4 (VBUS), J8.A9 (VBUS), J8.B4 (VBUS), J8.B9 (VBUS), U7.1 (OUT), U8.5 (VBUS)
POWER_IN: C69.1, R60.2, U7.5 (IN); also elsewhere on the board
fault_signal: R60.1, U7.3 (~FLT); also elsewhere on the board

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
